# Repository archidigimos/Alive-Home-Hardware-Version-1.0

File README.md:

# Alive-Home-Hardware-Version-1.0
Eagle schematics and Board files for the Initial version of Alive Home automation product. This version of product is powered by an Atmega MCU and is customised to be installed in Meghnad Saha Hall of Residence, IIT Kharagpur.

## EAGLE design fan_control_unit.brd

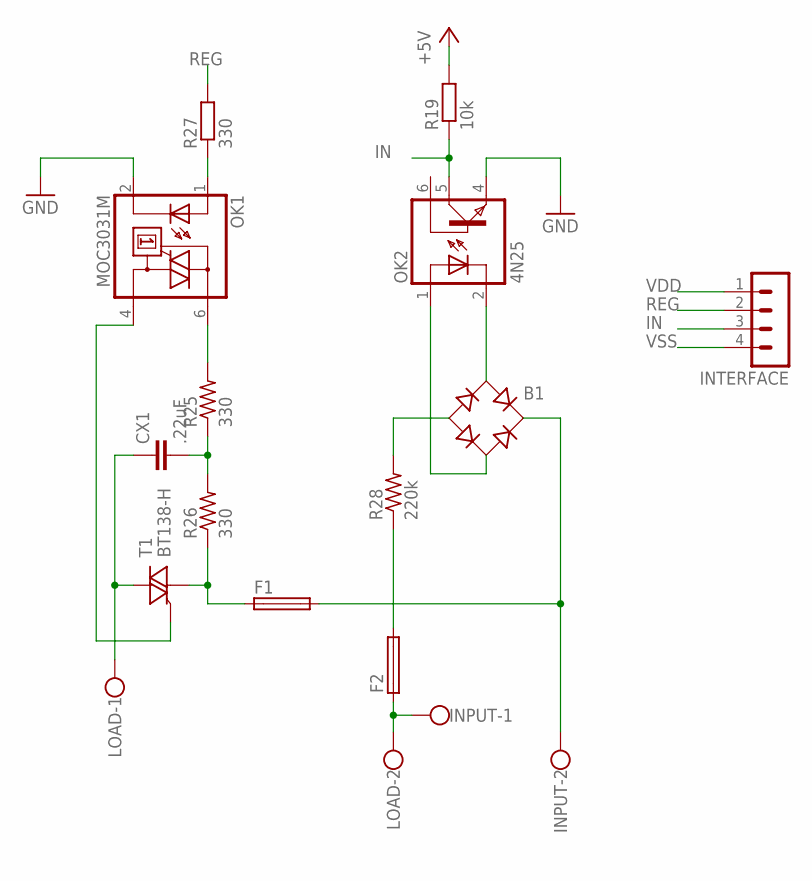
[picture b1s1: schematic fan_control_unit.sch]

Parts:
B1: RB1A
CX1: .22uF; C150-054X183
F1, F2: SH22,5A
INPUT: W237-102
INTERFACE: MA04-1
LOAD: W237-102
OK1: MOC3031M; DIL06
OK2: 4N25; DIL06
R19: 10k; R1206
R25, R26: 330; 0207/15
R27: 330; R1206
R28: 220k; 0207/15
T1: BT138-H; TO220BH

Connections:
GATE: OK1.4 (A1), T1.G
IN: INTERFACE.3, OK2.5 (COL), R19.1
unnamed: F1.1, R26.1, T1.T1 (A1)
unnamed: F2.2, R28.1
unnamed: F2.1, INPUT.1, LOAD.2
unnamed: B1.AC1, OK2.2 (C)
unnamed: B1.AC2, OK2.1 (A)
unnamed: OK1.6 (A2), R25.2
unnamed: CX1.1, LOAD.1, T1.T2 (A2)
unnamed: OK1.1 (A), R27.1
unnamed: CX1.2, R25.1, R26.2
unnamed: B1.-, R28.2
unnamed: B1.+, F1.2, INPUT.2
REG: INTERFACE.2, R27.2
VDD: INTERFACE.1, R19.2
VSS: INTERFACE.4, OK1.2 (C), OK2.4 (EMI)

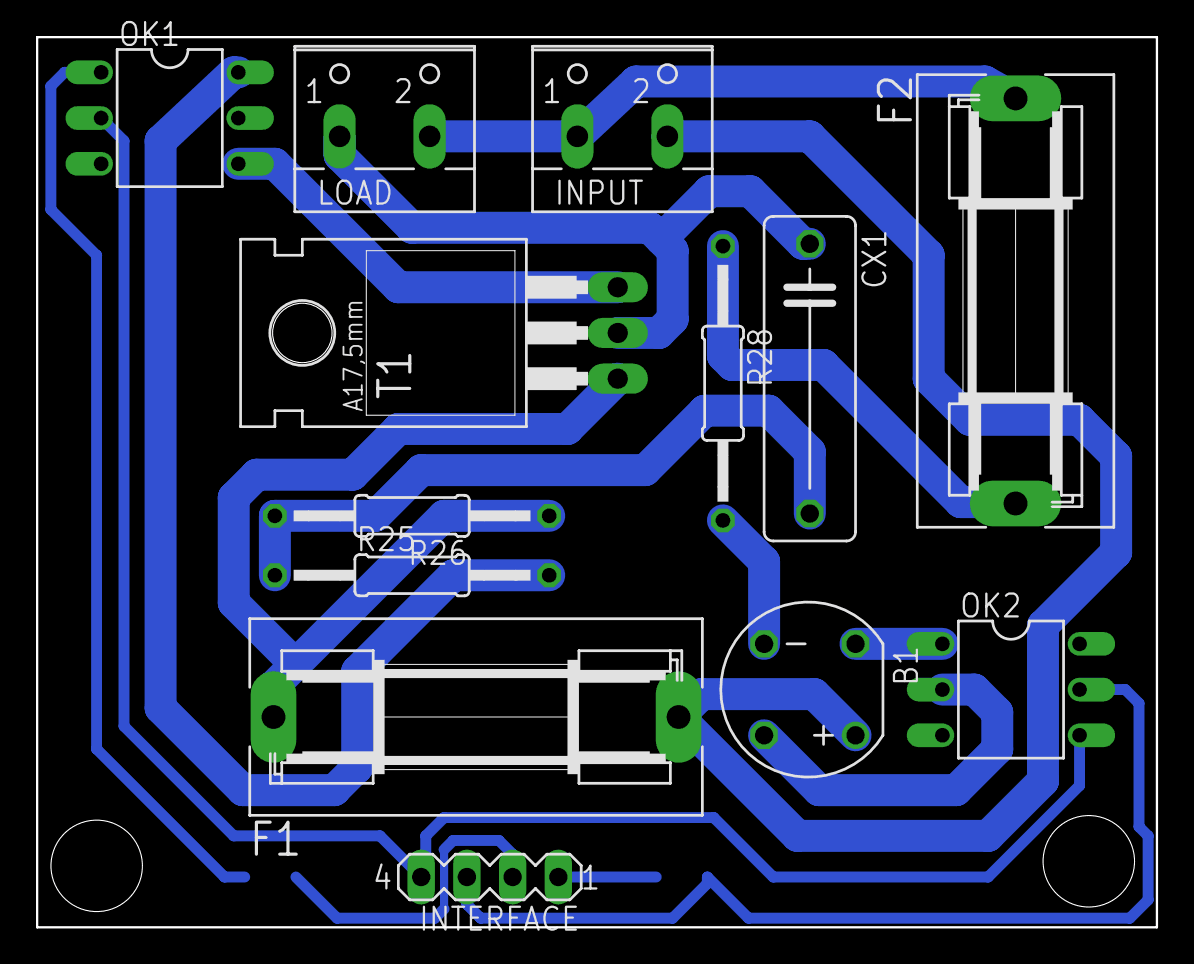
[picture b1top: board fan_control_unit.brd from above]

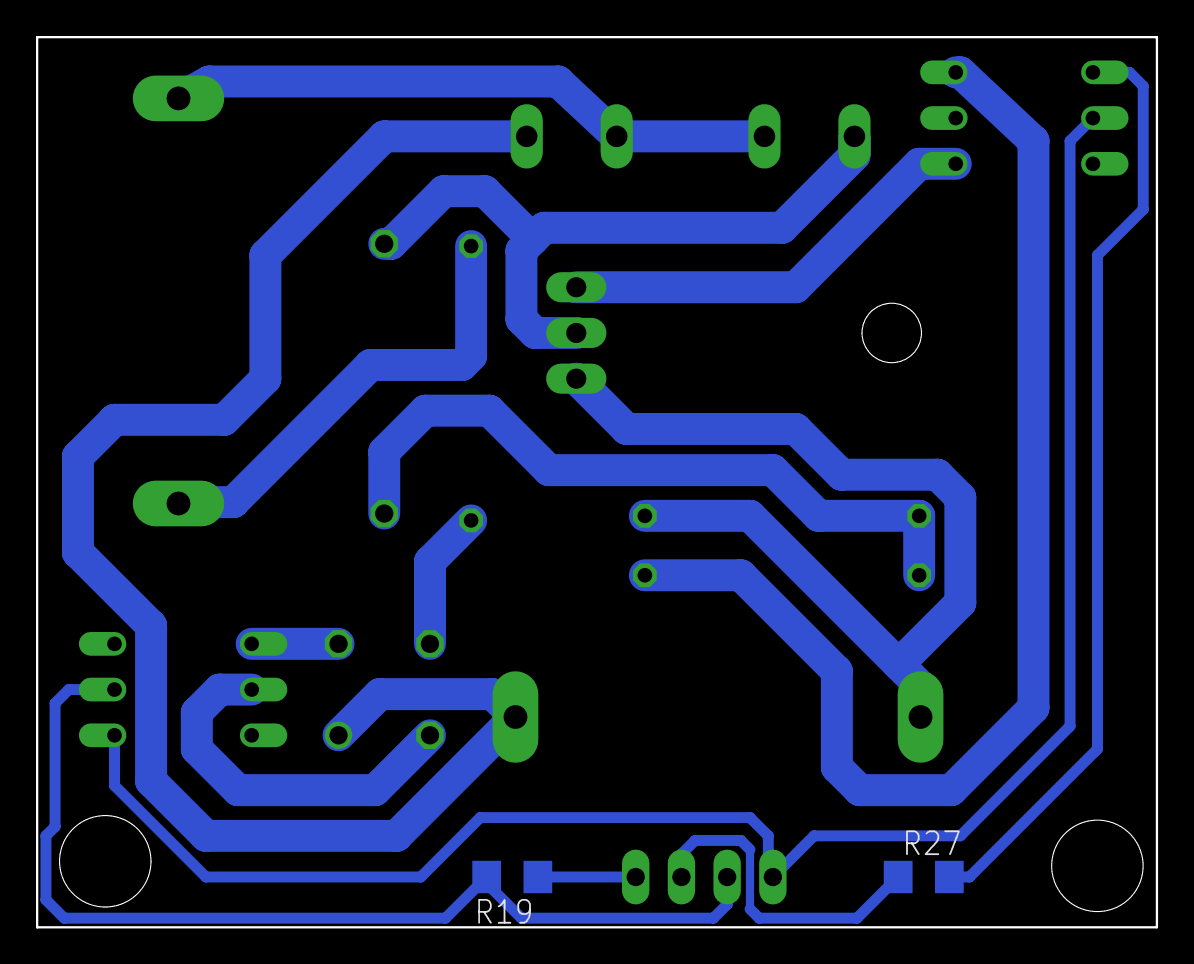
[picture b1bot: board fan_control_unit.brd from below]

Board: 2 copper layers, 62.2 x 49.5 mm, 15 parts (2 on the bottom side), 16 nets.

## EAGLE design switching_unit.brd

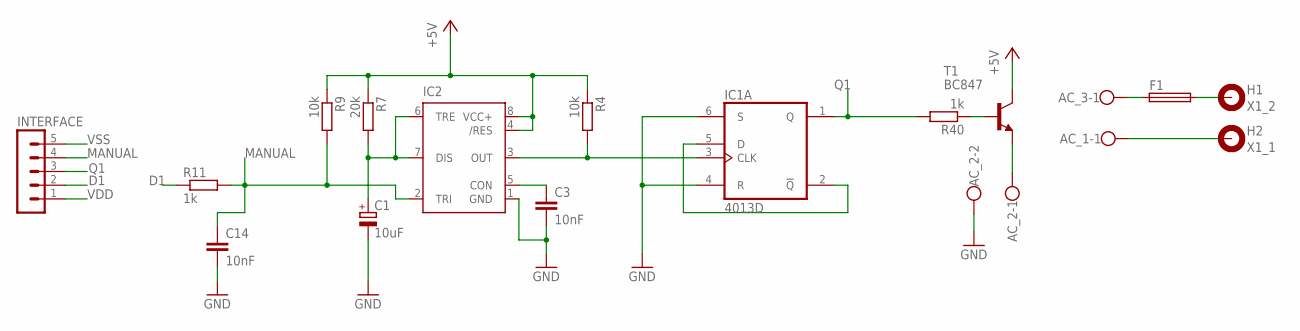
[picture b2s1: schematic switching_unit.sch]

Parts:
AC_1, AC_2, AC_3: W237-102
C1: 10uF; 153CLV-0405
C3, C14: 10nF; C1206
F1: SH22,5A
H1: X1_2; 2,8-PAD
H2: X1_1; 2,8-PAD
IC1: 4013D; SO14
IC2: NE555D; SO08
INTERFACE: MA05-1
R4, R9: 10k; R1206
R7: 20k; R1206
R11, R40: 1k; R1206
T1: BC847; SOT23

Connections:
D1: INTERFACE.2, R11.1
MANUAL: C14.1, IC2.2 (TRI), INTERFACE.4, R9.2, R11.2
unnamed: R40.1, T1.1 (B)
unnamed: F1.2, H1.B2,8
unnamed: AC_1.1, H2.B2,8
unnamed: AC_2.1, T1.2 (E)
unnamed: IC1.2 (!Q), IC1.5 (D)
unnamed: IC1.3 (CLK), IC2.3 (OUT), R4.2
unnamed: C1.+, IC2.6 (TRE), IC2.7 (DIS), R7.2
unnamed: C3.1, IC2.5 (CON)
unnamed: AC_3.1, F1.1
Q1: IC1.1 (Q), INTERFACE.3, R40.2
VDD: IC1.14 (VDD), IC2.4 (/RES), IC2.8 (VCC+), INTERFACE.1, R4.1, R7.1, R9.1, T1.3 (C)
VSS: AC_2.2, C1.-, C3.2, C14.2, IC1.4 (R), IC1.6 (S), IC1.7 (VSS), IC2.1 (GND), INTERFACE.5

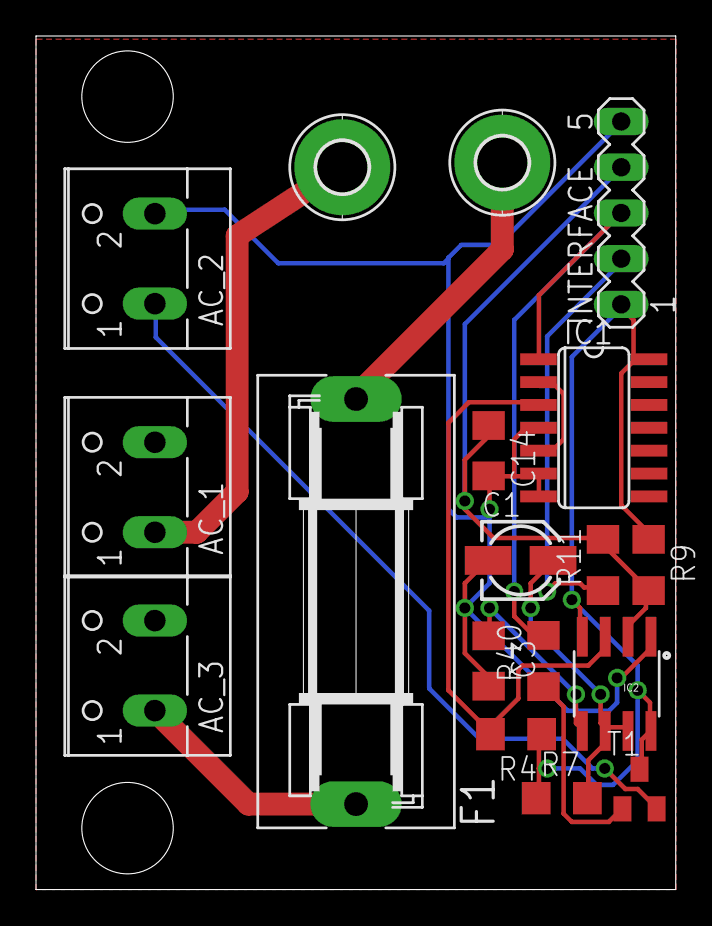
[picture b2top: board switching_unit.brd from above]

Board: 2 copper layers, 35.5 x 47.4 mm, 18 parts (0 on the bottom side), 14 nets.

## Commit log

2017-08-08 :lollipop: Added .gitattributes & .gitignore files
2017-08-08 Screenshot

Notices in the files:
parts and their libraries:
SparkFun-AnalogIC: Licensing:Creative Commons ShareAlike 4.0 International - https://creativecommons.org/licenses/by-sa/4.0
